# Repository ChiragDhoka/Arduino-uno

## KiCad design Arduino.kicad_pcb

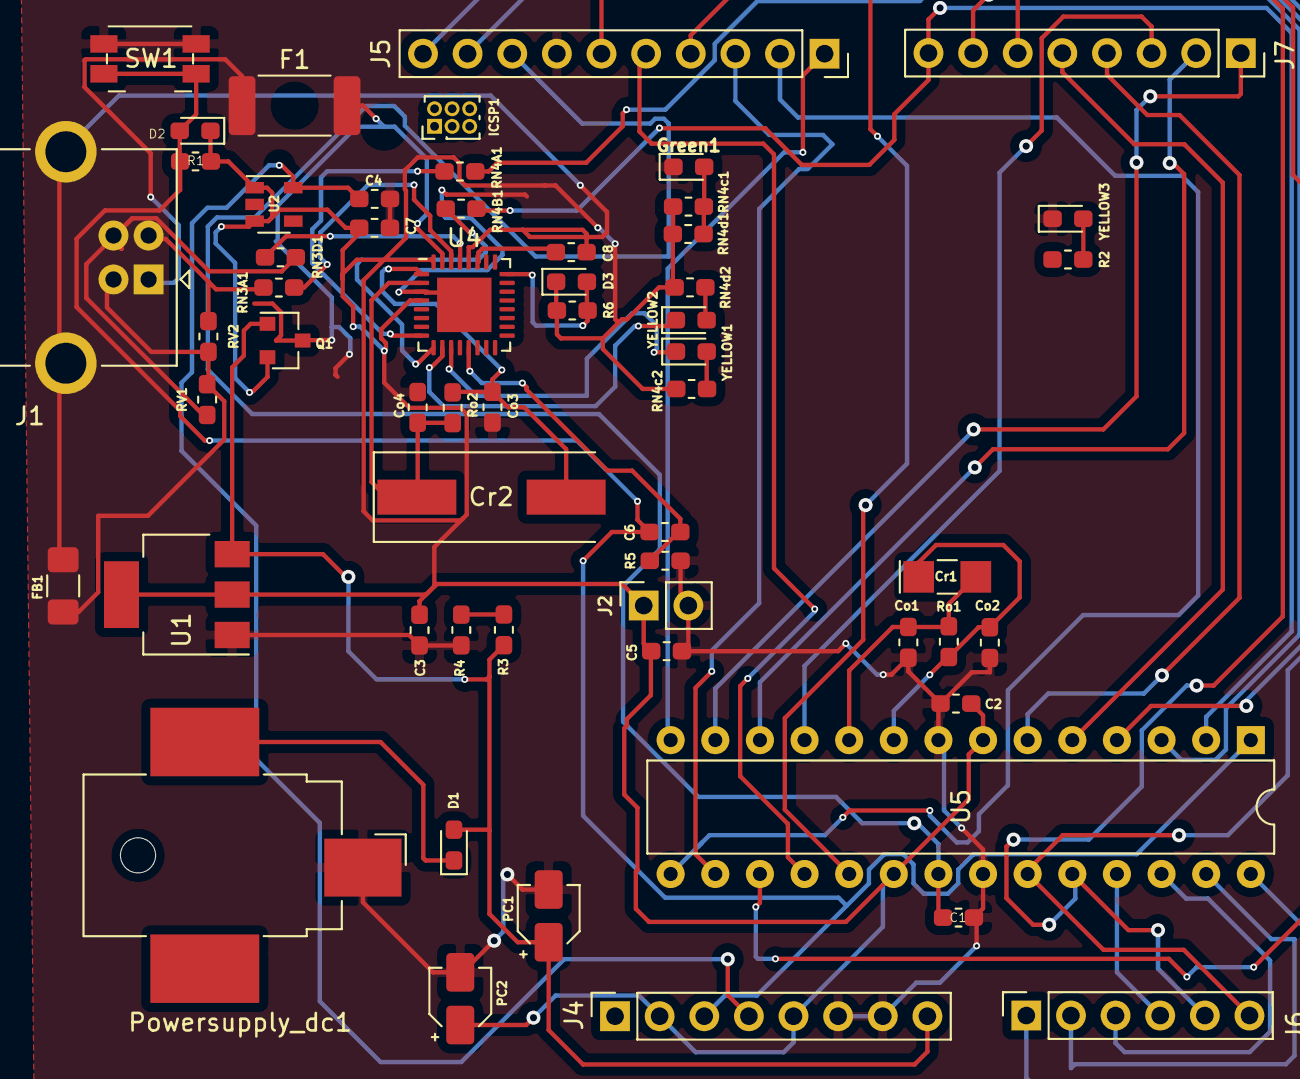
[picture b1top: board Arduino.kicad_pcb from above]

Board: 2 copper layers, 57 parts (0 on the bottom side), 51 nets.

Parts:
C1, C2, C3, C5, C6, C7: 100n; C_0603_1608Metric_Pad1.05x0.95mm_HandSolder
C4: 1u; C_0603_1608Metric_Pad1.05x0.95mm_HandSolder
C8: 1U; C_0603_1608Metric_Pad1.05x0.95mm_HandSolder
Co1, Co2, Co3, Co4: 22p; C_0603_1608Metric_Pad1.05x0.95mm_HandSolder
Cr1: 16MHz; Crystal_SMD_EuroQuartz_EQ161-2Pin_3.2x1.5mm_HandSoldering
Cr2: 16MHz; Crystal_SMD_HC49-SD
D1: DIODE; D_0603_1608Metric_Pad1.05x0.95mm_HandSolder
D2, D3: D; D_0603_1608Metric_Pad1.05x0.95mm_HandSolder
F1: 500mA; Fuse_2512_6332Metric_Pad1.52x3.35mm_HandSolder
FB1: BLM21PG2215N1D; Fuse_1206_3216Metric_Pad1.42x1.75mm_HandSolder
Green1: ON; LED_0603_1608Metric_Pad1.05x0.95mm_HandSolder
ICSP1: 02x03; PinHeader_2x03_P1.00mm_Vertical
J1: USB_B_Micro; USB_B_OST_USB-B1HSxx_Horizontal
J2: Screw_Terminal_01x02; PinSocket_1x02_P2.54mm_Vertical
J4, J7: Screw_Terminal_01x8; PinSocket_1x08_P2.54mm_Vertical
J5: Screw_Terminal_01x10; PinSocket_1x10_P2.54mm_Vertical
J6: Screw_Terminal_01x06; PinSocket_1x06_P2.54mm_Vertical
PC1, PC2: 47u; CP_Elec_3x5.4
Powersupply_dc1: Barrel_Jack; BarrelJack_CUI_PJ-036AH-SMT_Horizontal
Q1: DMG2301L; SOT-23
R1, R3, R4: 10k; R_0603_1608Metric_Pad1.05x0.95mm_HandSolder
R2, R5: 1k; R_0603_1608Metric_Pad1.05x0.95mm_HandSolder
R6: R; R_0603_1608Metric_Pad1.05x0.95mm_HandSolder
RN3A1, RN3D1: 22R; R_0603_1608Metric_Pad1.05x0.95mm_HandSolder
RN4A1, RN4B1: 1K; R_0603_1608Metric_Pad1.05x0.95mm_HandSolder
RN4c1, RN4c2, RN4d1, RN4d2: 1k; R_0603_1608Metric_Pad1.05x0.95mm_HandSolder
RV1, RV2: Varistor; L_0603_1608Metric_Pad1.05x0.95mm_HandSolder
Ro1, Ro2: 1M; R_0603_1608Metric_Pad1.05x0.95mm_HandSolder
SW1: SW_Push_Dual; Panasonic_EVQPUJ_EVQPUA
U1: NCP1117-5.0_SOT223; SOT-223-3_TabPin2
U2: LP2985-3.3; SOT-23-5
U4: ATmega16U2-MU; QFN-32-1EP_5x5mm_P0.5mm_EP3.1x3.1mm
U5: ATmega328P-PU; DIP-28_W7.62mm
YELLOW1, YELLOW2: ON; LED_0603_1608Metric_Pad1.05x0.95mm_HandSolder
YELLOW3: LED; LED_0603_1608Metric_Pad1.05x0.95mm_HandSolder

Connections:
+5V: C2.1, C3.1, C5.1, C7.1, D2.1, D3.1, J2.1, J4.2, J4.5, PC2.1, Q1.2, R1.1, R6.1, RN4c1.2, RN4c2.2, RN4d1.2, RN4d2.2, U1.2, U2.1, U2.3, U4.4, U4.32, U5.7, U5.20
/+3v3: C4.1, J4.4, U2.5
/AREF: C1.1, J5.8, U5.21
/D+: RN3D1.1, U4.29
/D-: RN3A1.2, U4.30
/UGND: C8.2, FB1.2, J1.5, U4.28
/USBVCC: F1.2, Q1.3, U4.31
/VIN: D1.2, J4.8, PC1.1, Q1.1, R3.1, U1.3
AD0: J6.1, U5.28
AD1: J6.2, U5.27
AD2: J6.3, U5.26
AD3: J6.4, U5.25
AD4,SDA: J5.9, J6.5, U5.24
AD5,SCL: J5.10, J6.6, U5.23
DTR: C6.2, R5.1, U4.13
GND: C1.2, C2.2, C3.2, C4.2, C5.2, C7.2, Co1.1, Co2.2, Co3.1, Co4.2, Green1.1, J2.2, J4.6, J4.7, J5.7, PC1.2, PC2.2, Powersupply_dc1.1, R4.2, R5.2, SW1.2, U1.1, U4.3, U4.33, U5.8, U5.22, YELLOW3.1
IO0: J7.1, U5.13
IO1: J7.2, U5.12
IO2: J7.3, U5.11
IO3: J7.4, U5.6
IO4: J7.5, U5.5
IO5: J7.6, U5.4
IO6: J7.7, RN4A1.1, U5.3
IO7: J7.8, RN4B1.1, U5.2
IO8: J5.1, U5.14
IO9: J5.2, U5.15
IO10,SS: J5.3, U5.16
IO11,MOSI: J5.4, U5.17
IO12,MISO: J5.5, U5.18
IO13,SCK: J5.6, U5.19
M8RXD: RN4B1.2, U4.9
M8TXD: RN4A1.2, U4.8
unnamed: C8.1, U4.27
unnamed: Co1.2, Cr1.2, Ro1.2, U5.10
unnamed: Co2.1, Cr1.1, Ro1.1, U5.9
unnamed: Co3.2, Cr2.2, Ro2.2, U4.1
unnamed: Co4.1, Cr2.1, Ro2.1, U4.2
unnamed: D1.1, Powersupply_dc1.2
unnamed: D3.2, R6.2, U4.24
unnamed: F1.1, J1.1
unnamed: FB1.1, J1.4, RV1.2, RV2.2
unnamed: Green1.2, RN4c1.1, RN4d1.1
unnamed: J1.2, RN3A1.1, RV2.1
unnamed: J1.3, RN3D1.2, RV1.1
unnamed: R2.2, YELLOW3.2
unnamed: R3.2, R4.1
unnamed: RN4c2.1, YELLOW1.2
unnamed: RN4d2.1, YELLOW2.2
RESET: C6.1, D2.2, J4.3, R1.2, SW1.1, U5.1
RXLED: U4.10, YELLOW2.1
TXLED: U4.11, YELLOW1.1
